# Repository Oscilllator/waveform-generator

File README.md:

# Why does it exist

The purpose of this waveform generator is to give your computer the ability to make waves. It should be thought of as a waveform interface for your computer, like a network interface or an audio interface. The computer streams waveforms continuously to the generator, the generator itself has no memory.
I created this because I don't like the software interface to any other waveform generator I have used.

You use it like this:
```python
import numpy as np
import awglib
awg = awglib.awg()
samples = np.sin(np.linspace(0, 2 * np.pi, 1000))
awg.send_volts(samples)
```

You can simply stream samples to it, or gate the sending of the samples on a trigger input. It also has two digital outputs which are embedded in the sample stream. You can use them like this:

```python
samples = np.sin(np.linspace(0, 2 * np.pi, 1000))
d0 = samples > 0.8
d1 = samples < -0.5
awg.send_volts(samples, digital=[d0, d1])
```

Which then would look like this:

This is useful for triggering your scope or other instruments.

## Specifications
| Parameter           | Value    |
|---------------------|----------|
| Samples rate        | 10 MSa/s |
| Rise/fall time      | 50 ns    |
| Max output current  | 600 mA   |
| Resolution          | 14 bit   |
| Digital outputs     | 2        |

The device also has a 16 bit digital output bus for debugging the fpga, and 8 LED's. The digital outputs come straight from the FPGA and so have no drive strength to speak of. You won't blow up the FPGA if you 50R terminate them, though.

It looks like this:

## Examples

### Scrolling text

This example is `examples/scrolling_text.py` and demonstrates some of the benefits of having a streaming setup - there is a lot of memory on your main computer as compared to any reasonable waveform generator.

This whole gif is one single waveform of about ~500MB over the wire. Several passes are made over the text, one for each letter section. The persistence of vision within the oscilloscope stitches them together, producing whole letters. Once the whole text has been emitted the waveform is then re-emitted with the embedded digital trigger pulse sent with a slightly different time delay. This is easily done by simply concatenating the waveform to itself many times, attaching a shifted version of the trigger array each time. This wastes a lot of memory but was trivial to implement.

## Setup
### From a new computer
#### Udev rules
The USB chip is a FT232, but I have programmed it to have a custom Vid and Pid, so that the linux kernel doesn't grab it.

This script sets up the udev rules so the device can be opened without root:

```./ft/setup.sh```
#### Python library
I install it like this from the root directory of the repository:

```pip install -e .```

That way the library is loaded from the repository on startup rather than being copied to an install directory. Ask your favourite AI what's right for you.

### From a bare PCB
The EEPROM of the FT2332 needs to be programmed so that it will output in synchronous FIFO mode, and so that the default vendor ID and product ID is changed, preventing the linux kernel from recognising it.

```./program_eeprom.sh```

## Repository contents
This repository contains the kicad files, RTL, and API to operate a waveform generator.

### Hardware
I got the PCB's assembled with JLCPCB's 6 layer service with plated over vias, to make the routing of the FPGA BGA package easy.
The device uses an FT232 as a USB->FIFO adapter, that currently streams exclusively in the PC->FT232 direction. Use of the device in this mode requires flashing the eeprom, for which a utility is also included.

### RTL
The Flow of information is as follows:

PC -> FT232 -> ECP5 FPGA -> AD9744 DAC -> Amplifier

The RTL for the fpga is provided, which uses the excellent repository [here](https://github.com/WangXuan95/FPGA-ftdi245fifo/tree/main?tab=readme-ov-file#cn) to interface with the FT232. The AD9744 has a simple parallel interface, so that also makes things easy.

The simulation can be run as a unit test with `./run_tests.sh`

### API
The waveform generator is interfaces with in python, though I may [port it to C](https://harrydb.com/Continuous-waveforms) at some point.

### Bringup notes

This device was designed as a series of sub-boards. It started as a [Colorlight DAC](https://harrydb.com/20240902-A-good-waveform-generator) dev board and the [amplifier stage](https://harrydb.com/20250103-awg-buffer-bringup). These were then merged into a [Single PCB](https://harrydb.com/20250403-AWG-2-bringup). There are [various other notes](https://harrydb.com/#waveform-generator) on my lab notes page that detail other parts of the design process.

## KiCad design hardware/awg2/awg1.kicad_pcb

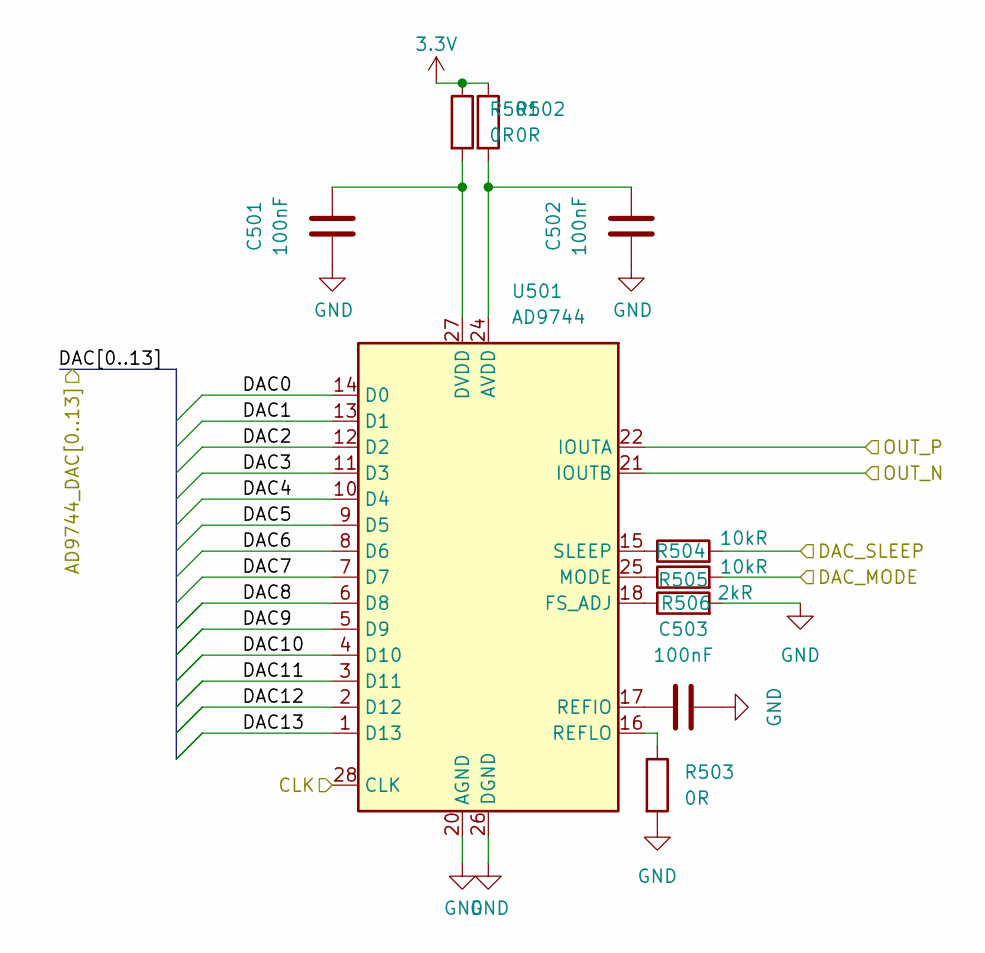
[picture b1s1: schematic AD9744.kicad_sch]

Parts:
C501, C502, C503: 100nF; R_0603_1608Metric; LCSC C1634
R501, R502: 0R; R_0603_1608Metric
R503: 0R; R_0603_1608Metric; LCSC C22787
R504, R505: 10kR; R_0603_1608Metric; LCSC C22787
R506: 2kR; R_0603_1608Metric; LCSC C22787
U501: AD9744; TSSOP-28_4.4x9.7mm_P0.65mm

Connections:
3.3V: R501.1, R502.1; also elsewhere on the board
/AD9744/CLK: U501.28 (CLK); also elsewhere on the board
/AD9744/DAC0: U501.14 (D0); also elsewhere on the board
/AD9744/DAC1: U501.13 (D1); also elsewhere on the board
/AD9744/DAC2: U501.12 (D2); also elsewhere on the board
/AD9744/DAC3: U501.11 (D3); also elsewhere on the board
/AD9744/DAC4: U501.10 (D4); also elsewhere on the board
/AD9744/DAC5: U501.9 (D5); also elsewhere on the board
/AD9744/DAC6: U501.8 (D6); also elsewhere on the board
/AD9744/DAC7: U501.7 (D7); also elsewhere on the board
/AD9744/DAC8: U501.6 (D8); also elsewhere on the board
/AD9744/DAC9: U501.5 (D9); also elsewhere on the board
/AD9744/DAC10: U501.4 (D10); also elsewhere on the board
/AD9744/DAC11: U501.3 (D11); also elsewhere on the board
/AD9744/DAC12: U501.2 (D12); also elsewhere on the board
/AD9744/DAC13: U501.1 (D13); also elsewhere on the board
/AD9744/DAC_MODE: R505.2; also elsewhere on the board
/AD9744/DAC_SLEEP: R504.2; also elsewhere on the board
/AD9744/OUT_N: U501.21 (IOUTB); also elsewhere on the board
/AD9744/OUT_P: U501.22 (IOUTA); also elsewhere on the board
GND: C501.1, C502.1, C503.1, R503.2, R506.2, U501.20 (AGND), U501.26 (DGND); also elsewhere on the board
unnamed: C502.2, R502.2, U501.24 (AVDD)
unnamed: C501.2, R501.2, U501.27 (DVDD)
unnamed: R506.1, U501.18 (FS_ADJ)
unnamed: R505.1, U501.25 (MODE)
unnamed: C503.2, U501.17 (REFIO)
unnamed: R503.1, U501.16 (REFLO)
unnamed: R504.1, U501.15 (SLEEP)

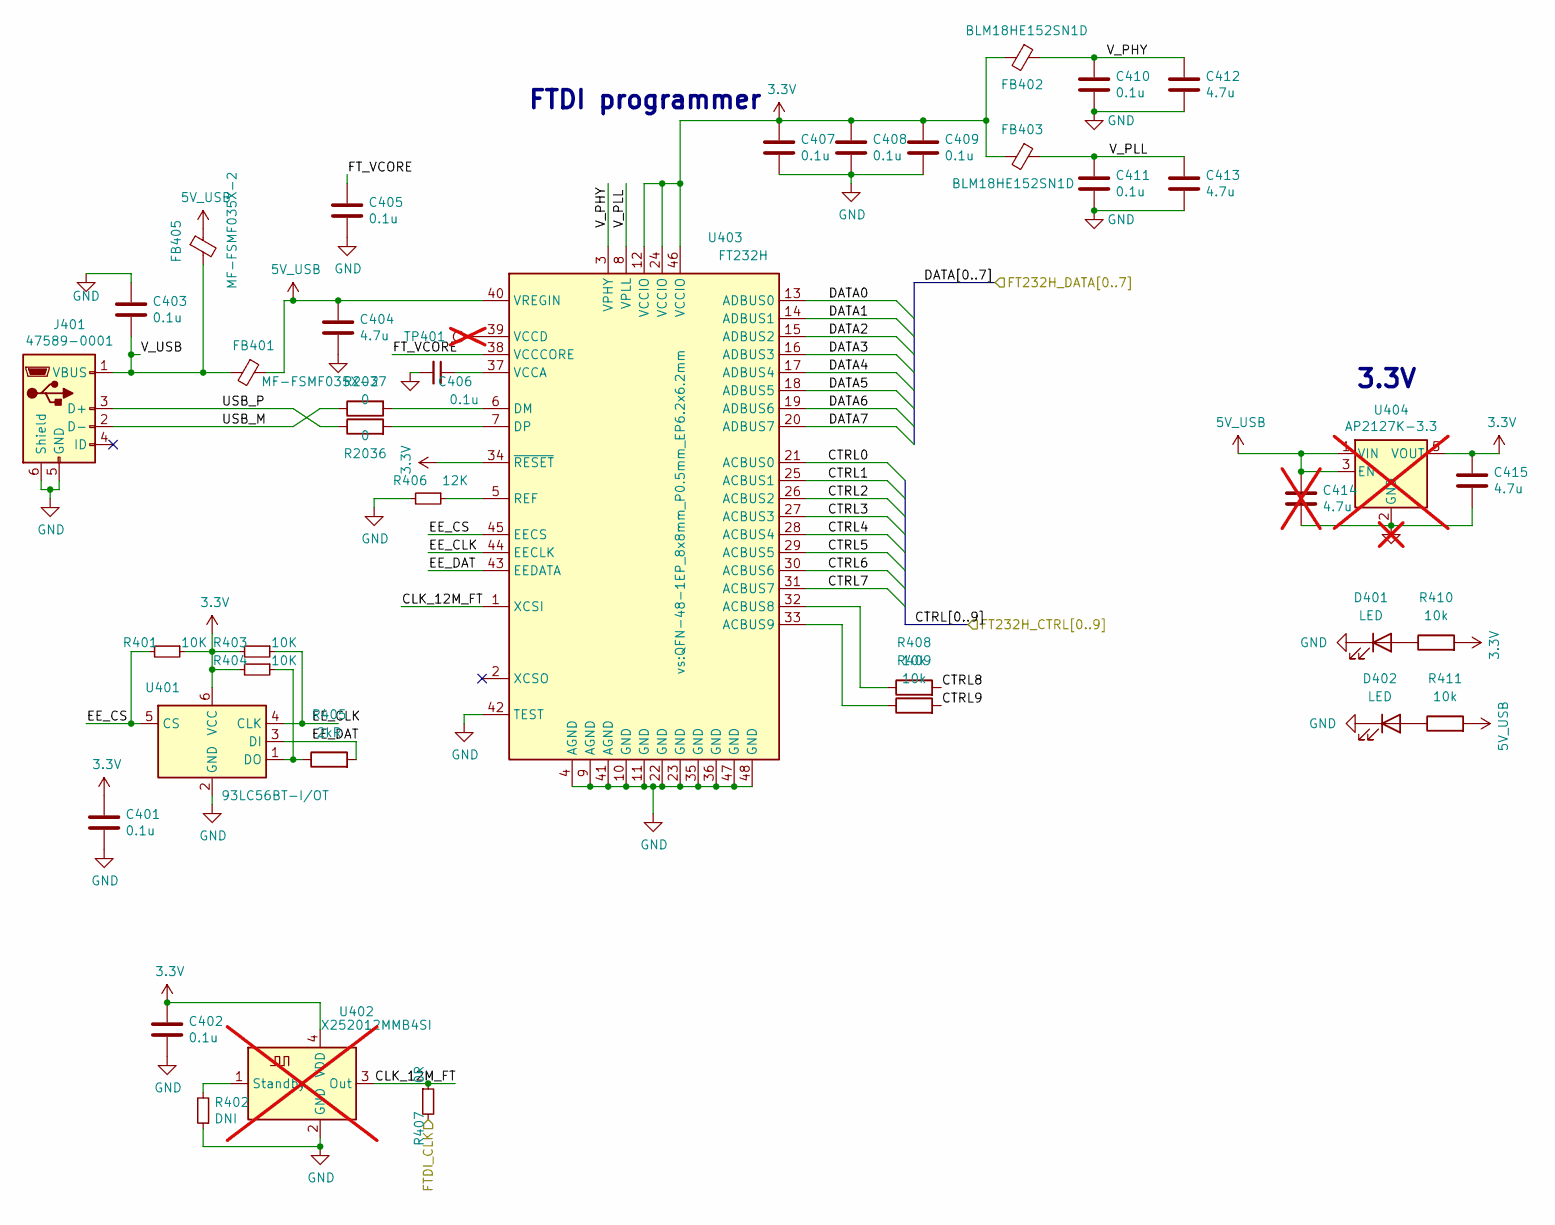
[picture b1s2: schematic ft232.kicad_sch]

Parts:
C401, C402, C403, C405, C406, C407, C408, C409, C410, C411: 0.1u; C_0603_1608Metric
C404, C412, C413, C415: 4.7u; C_0603_1608Metric
C414: 4.7u; C_0603_1608Metric; not fitted
D401, D402: LED; D_0603_1608Metric; LCSC C2286
FB401, FB405: MF-FSMF035X-2; L_0603_1608Metric
FB402, FB403: BLM18HE152SN1D; L_0603_1608Metric
J401: 47589-0001; USB_Micro-B_Molex_47346-0001
R401, R403, R404: 10K; R_0603_1608Metric
R402: DNI; R_0603_1608Metric
R405: 2kR; R_0402_1005Metric
R406: 12K; R_0603_1608Metric
R407: 0R; R_0603_1608Metric
R408, R409, R410, R411: 10k; R_0603_1608Metric; LCSC C25804
R2036, R2037: 0; R_0603_1608Metric; LCSC C21189
TP401: TestPoint; TestPoint_Pad_D1.0mm; not fitted
U401: 93LC56BT-I/OT; SOT-23-6
U402: X252012MMB4SI; Oscillator_SMD_Abracon_ASDMB-4Pin_2.5x2.0mm; not fitted
U403: FT232H; QFN-48-1EP_8x8mm_P0.5mm_EP6.2x6.2mm
U404: AP2127K-3.3; SOT-23-5; not fitted

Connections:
3.3V: C401.1, C402.1, C407.1, C408.1, C409.1, C415.1, FB402.2, FB403.2, R401.1, R403.2, R404.2, R410.2, U401.6 (VCC), U402.4 (VDD), U403.12 (VCCIO), U403.24 (VCCIO), U403.34 (~RESET), U403.46 (VCCIO), U404.5 (VOUT); also elsewhere on the board
5V_USB: C404.1, C414.1, FB401.1, FB405.1, R411.2, U403.40 (VREGIN), U404.1 (VIN), U404.3 (EN); also elsewhere on the board
/fpga/CTRL0: U403.21 (ACBUS0); also elsewhere on the board
/fpga/CTRL1: U403.25 (ACBUS1); also elsewhere on the board
/fpga/CTRL2: U403.26 (ACBUS2); also elsewhere on the board
/fpga/CTRL3: U403.27 (ACBUS3); also elsewhere on the board
/fpga/CTRL4: U403.28 (ACBUS4); also elsewhere on the board
/fpga/CTRL5: U403.29 (ACBUS5); also elsewhere on the board
/fpga/CTRL6: U403.30 (ACBUS6); also elsewhere on the board
/fpga/CTRL7: U403.31 (ACBUS7); also elsewhere on the board
/fpga/CTRL8: R408.2; also elsewhere on the board
/fpga/CTRL9: R409.2; also elsewhere on the board
/fpga/DATA0: U403.13 (ADBUS0); also elsewhere on the board
/fpga/DATA1: U403.14 (ADBUS1); also elsewhere on the board
/fpga/DATA2: U403.15 (ADBUS2); also elsewhere on the board
/fpga/DATA3: U403.16 (ADBUS3); also elsewhere on the board
/fpga/DATA4: U403.17 (ADBUS4); also elsewhere on the board
/fpga/DATA5: U403.18 (ADBUS5); also elsewhere on the board
/fpga/DATA6: U403.19 (ADBUS6); also elsewhere on the board
/fpga/DATA7: U403.20 (ADBUS7); also elsewhere on the board
/fpga/FTDI_CLK: R407.2; also elsewhere on the board
/ft232/CLK_12M_FT: R407.1, U402.3 (Out), U403.1 (XCSI)
/ft232/EE_CLK: R403.1, U401.4 (CLK), U403.44 (EECLK)
/ft232/EE_CS: R401.2, U401.5 (CS), U403.45 (EECS)
/ft232/EE_DAT: R405.2, U401.3 (DI), U403.43 (EEDATA)
/ft232/FT_VCORE: C405.1, U403.38 (VCCCORE)
/ft232/USB_M: J401.2 (D-), R2036.1
/ft232/USB_P: J401.3 (D+), R2037.1
/ft232/V_PHY: C410.1, C412.1, FB402.1, U403.3 (VPHY)
/ft232/V_PLL: C411.1, C413.1, FB403.1, U403.8 (VPLL)
/ft232/V_USB: C403.2, FB401.2, FB405.2, J401.1 (VBUS)
GND: C401.2, C402.2, C403.1, C404.2, C405.2, C406.2, C407.2, C408.2, C409.2, C410.2, C411.2, C412.2, C413.2, C414.2, C415.2, D401.1 (K), D402.1 (K), J401.5 (GND), J401.6 (Shield), R402.1, R406.2, U401.2 (GND), U402.2 (GND), U403.4 (AGND), U403.9 (AGND), U403.10 (GND), U403.11 (GND), U403.22 (GND), U403.23 (GND), U403.35 (GND), U403.36 (GND), U403.41 (AGND), U403.42 (TEST), U403.47 (GND), U403.48 (GND), U404.2 (GND); also elsewhere on the board
unnamed: D401.2 (A), R410.1
unnamed: D402.2 (A), R411.1
unnamed: R404.1, R405.1, U401.1 (DO)
unnamed: R402.2, U402.1 (Standby)
unnamed: R408.1, U403.32 (ACBUS8)
unnamed: R409.1, U403.33 (ACBUS9)
unnamed: R2036.2, U403.6 (DM)
unnamed: R2037.2, U403.7 (DP)
unnamed: R406.1, U403.5 (REF)
unnamed: C406.1, U403.37 (VCCA)
unnamed: TP401.1, U403.39 (VCCD)

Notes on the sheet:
3.3V
FTDI programmer

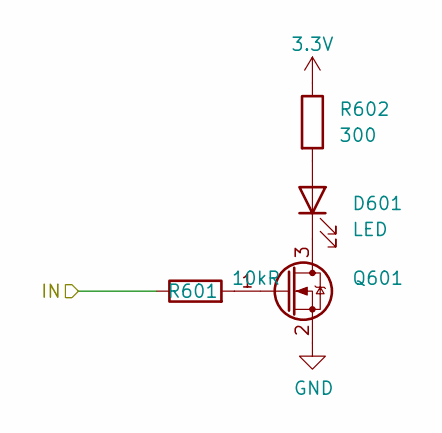
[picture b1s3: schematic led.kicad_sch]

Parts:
D601: LED; D_0603_1608Metric
Q601: Q_NMOS_Depletion_GSD; SOT-23; LCSC C20917
R601: 10kR; R_0603_1608Metric; LCSC C22787
R602: 300; R_0603_1608Metric_Pad0.98x0.95mm_HandSolder

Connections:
3.3V: R602.1; also elsewhere on the board
/lED0: R601.1; also elsewhere on the board
GND: Q601.2 (S); also elsewhere on the board
unnamed: D601.2 (A), R602.2
unnamed: D601.1 (K), Q601.3 (D)
unnamed: Q601.1 (G), R601.2

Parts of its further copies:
D701, D801, D901, D1001, D1101, D1201, D1301: LED; D_0603_1608Metric
Q701, Q801, Q901, Q1001, Q1101, Q1201, Q1301: Q_NMOS_Depletion_GSD; SOT-23; LCSC C20917
R701, R801, R901, R1001, R1101, R1201, R1301: 10kR; R_0603_1608Metric; LCSC C22787
R702, R802, R902, R1002, R1102, R1202, R1302: 300; R_0603_1608Metric_Pad0.98x0.95mm_HandSolder

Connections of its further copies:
3.3V: R702.1, R802.1, R902.1, R1002.1, R1102.1, R1202.1, R1302.1; also elsewhere on the board
/lED1: R701.1; also elsewhere on the board
/lED2: R801.1; also elsewhere on the board
/lED3: R901.1; also elsewhere on the board
/lED4: R1001.1; also elsewhere on the board
/lED5: R1101.1; also elsewhere on the board
/lED6: R1201.1; also elsewhere on the board
/lED7: R1301.1; also elsewhere on the board
GND: Q701.2 (S), Q801.2 (S), Q901.2 (S), Q1001.2 (S), Q1101.2 (S), Q1201.2 (S), Q1301.2 (S); also elsewhere on the board
unnamed: D701.2 (A), R702.2
unnamed: D701.1 (K), Q701.3 (D)
unnamed: D801.2 (A), R802.2
unnamed: D801.1 (K), Q801.3 (D)
unnamed: D901.2 (A), R902.2
unnamed: D901.1 (K), Q901.3 (D)
unnamed: D1001.2 (A), R1002.2
unnamed: D1001.1 (K), Q1001.3 (D)
unnamed: D1101.2 (A), R1102.2
unnamed: D1101.1 (K), Q1101.3 (D)
unnamed: D1201.2 (A), R1202.2
unnamed: D1201.1 (K), Q1201.3 (D)
unnamed: D1301.2 (A), R1302.2
unnamed: D1301.1 (K), Q1301.3 (D)
unnamed: Q701.1 (G), R701.2
unnamed: Q801.1 (G), R801.2
unnamed: Q901.1 (G), R901.2
unnamed: Q1001.1 (G), R1001.2
unnamed: Q1101.1 (G), R1101.2
unnamed: Q1201.1 (G), R1201.2
unnamed: Q1301.1 (G), R1301.2

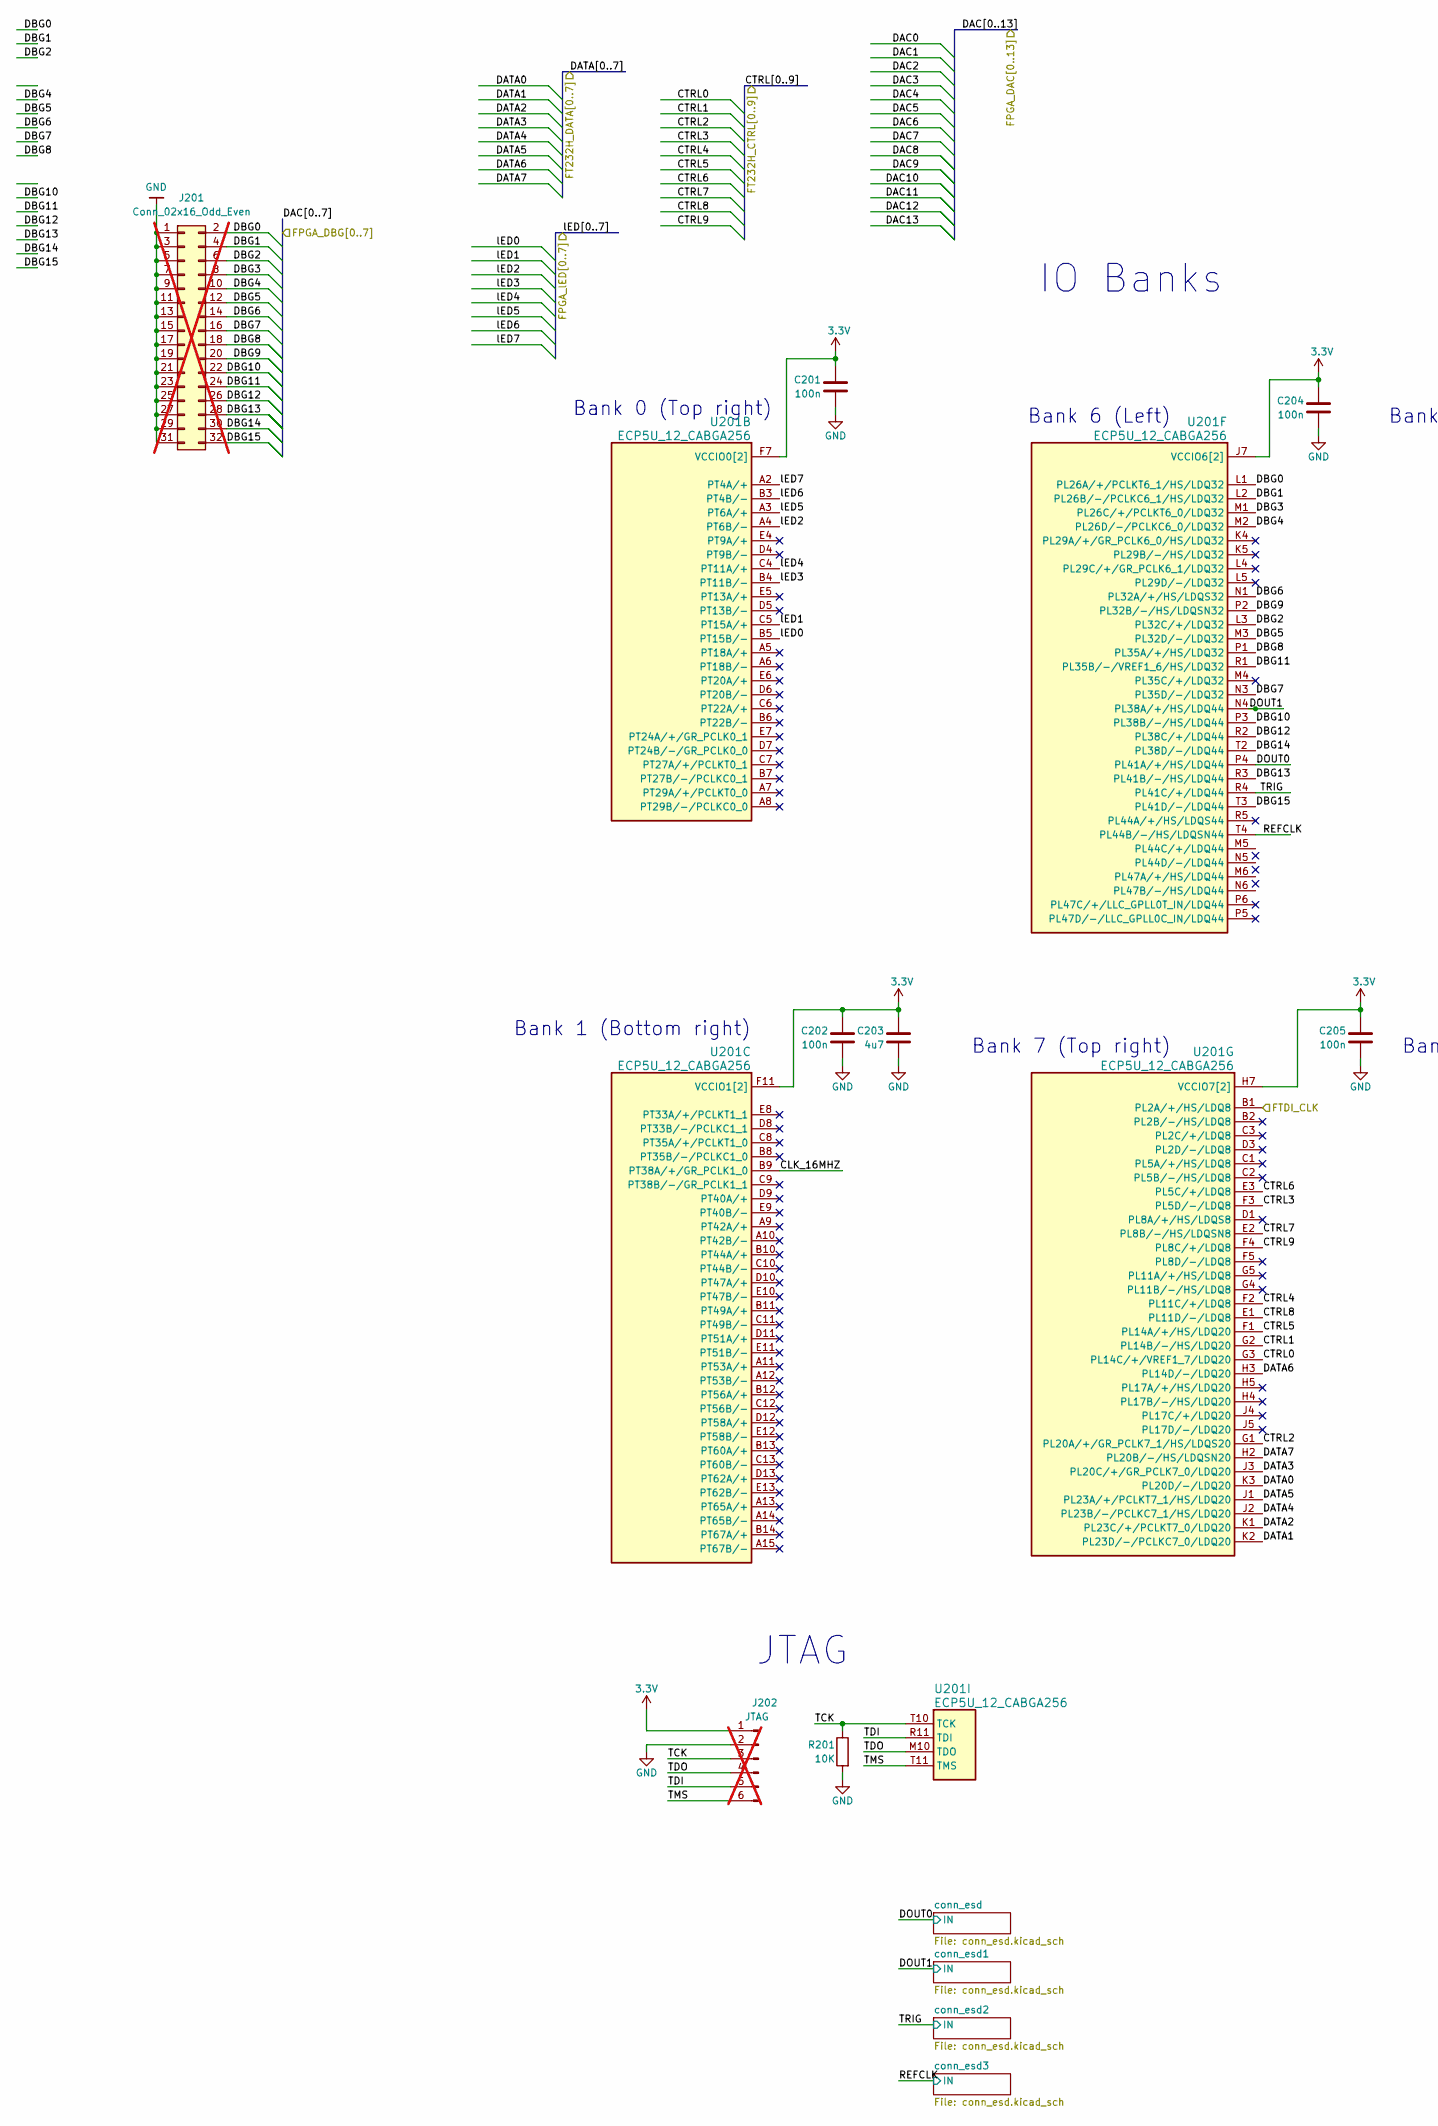
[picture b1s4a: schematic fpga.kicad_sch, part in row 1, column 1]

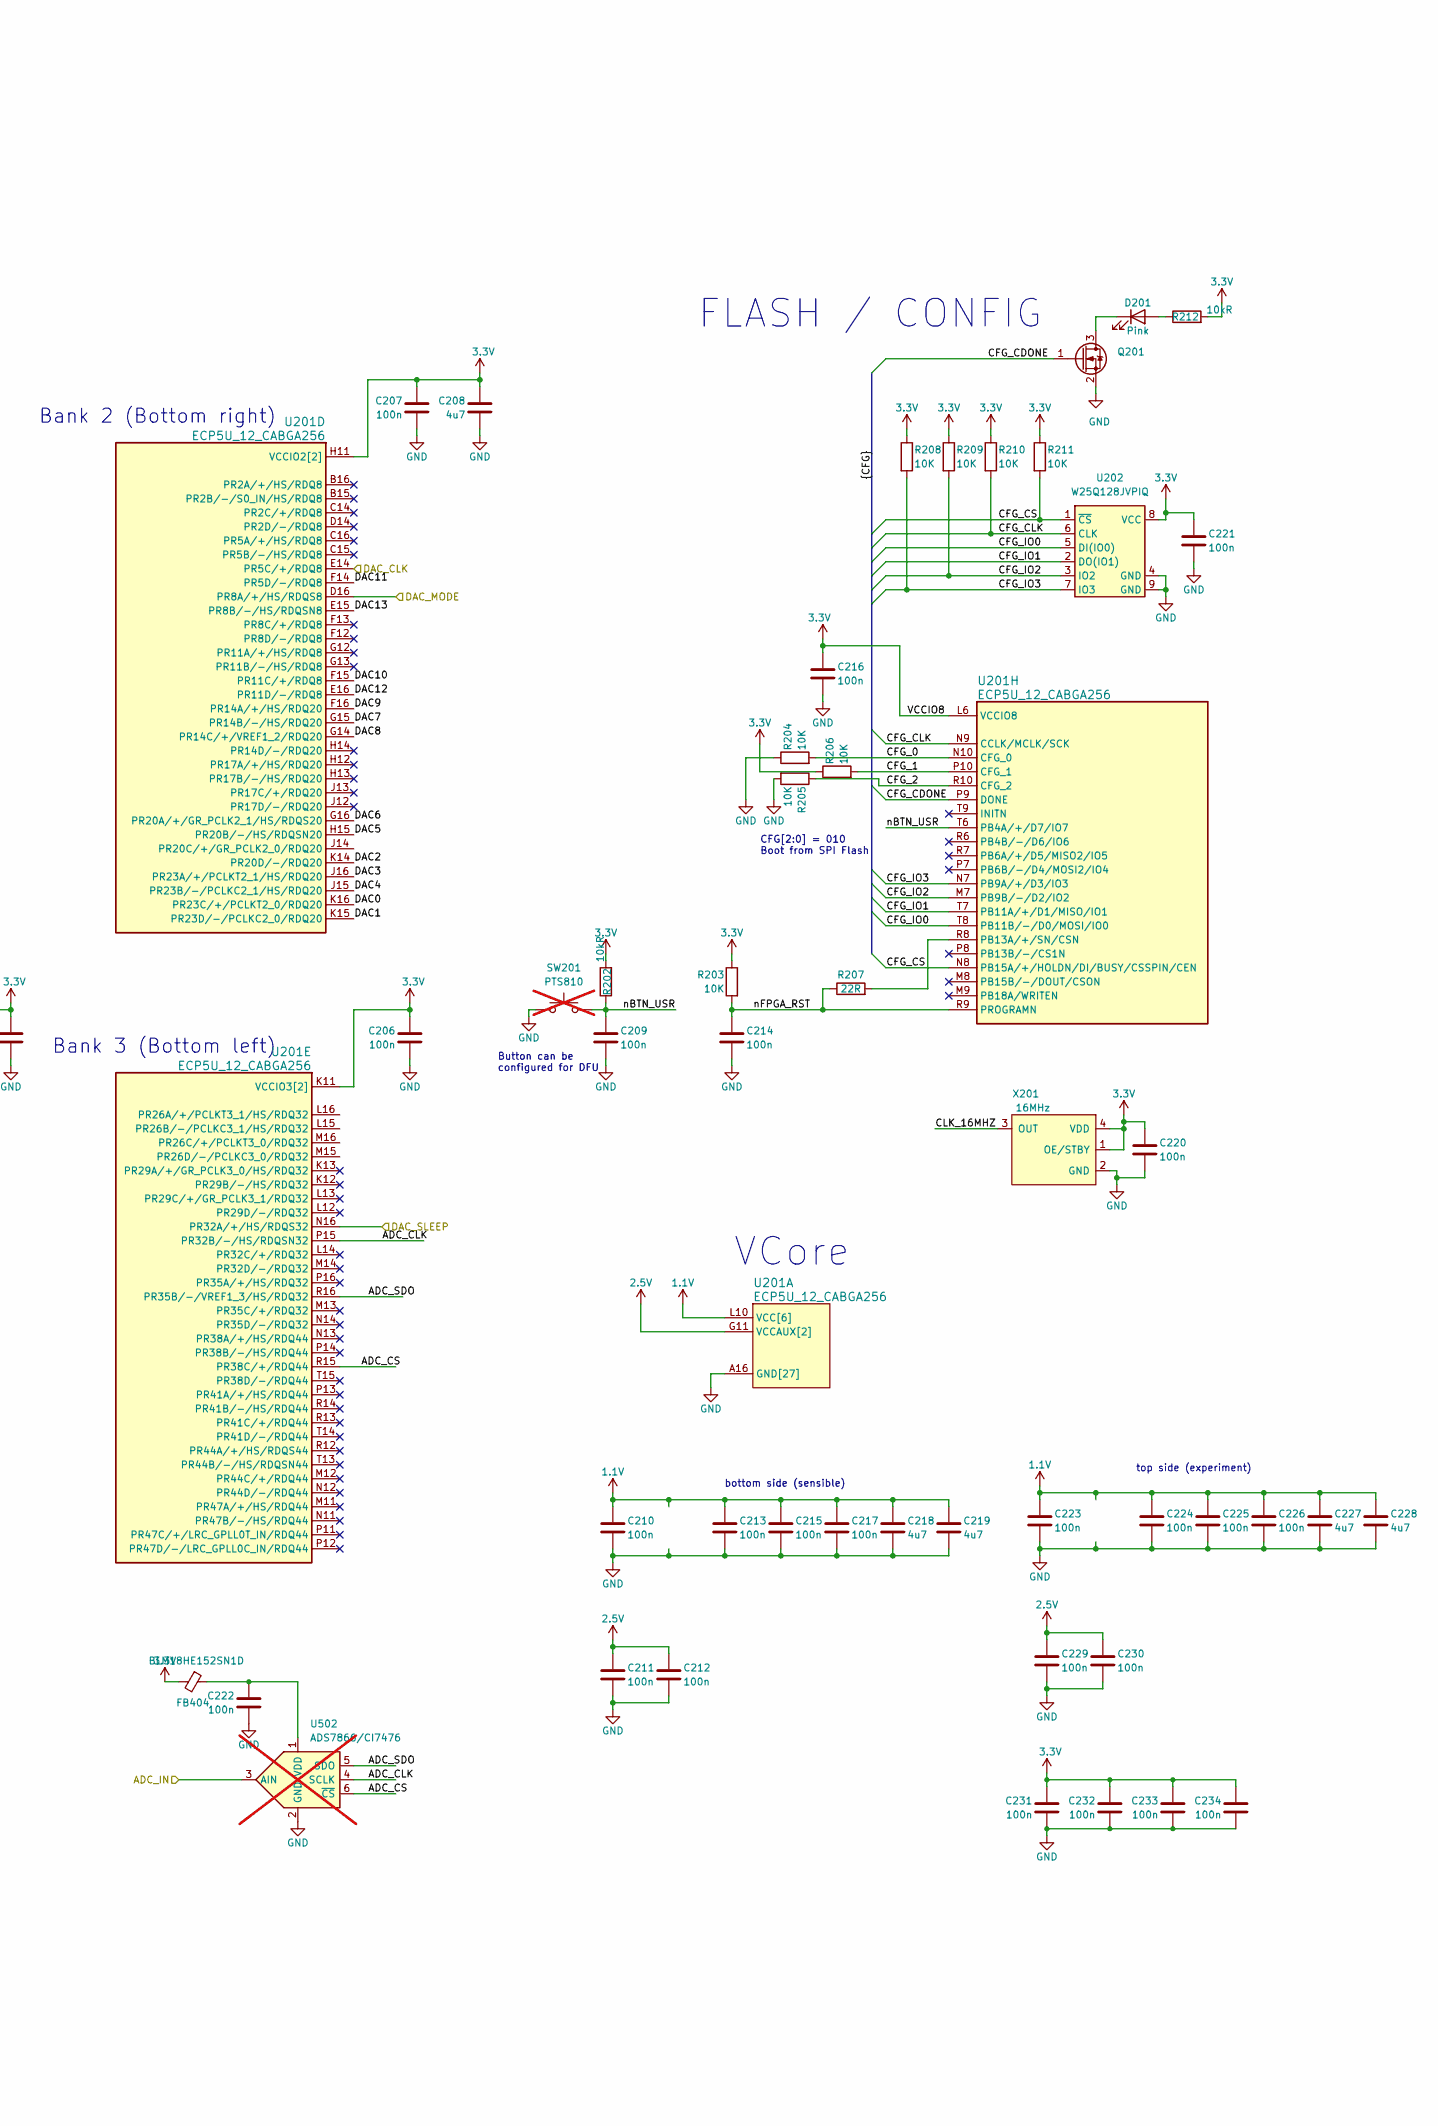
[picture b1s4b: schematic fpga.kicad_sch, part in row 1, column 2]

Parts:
C201, C202, C204, C205, C206, C207, C210, C211, C212, C213, C215, C216, C217, C220, C221, C222, C223, C224, C225, C226, C229, C230, C231, C232, C233, C234: 100n; C_0402_1005Metric; MPN CC0402KRX7R7BB104; LCSC C327009
C203, C208, C218, C219, C227, C228: 4u7; C_0402_1005Metric; MPN CC0402KRX5R6BB475; LCSC C326586
C209, C214: 100n; C_0402_1005Metric; MPN CC0402KRX7R7BB104
D201: Pink; LED_0603_1608Metric; MPN OSK40603C1E; LCSC C268294
FB404: BLM18HE152SN1D; L_0603_1608Metric
J201: Conn_02x16_Odd_Even; PinHeader_2x16_P2.54mm_Vertical; not fitted
J202: JTAG; STM_6_PIN_THT_Staggered; not fitted
Q201: Q_NMOS_Depletion_GSD; SOT-23; LCSC C20917
R201, R203, R204, R205, R206, R208, R209, R210, R211: 10K; R_0402_1005Metric; MPN RC0402JR-0710KL; LCSC C60489
R202, R212: 10kR; R_0603_1608Metric; LCSC C22787
R207: 22R; R_0402_1005Metric; MPN RC0402JR-0722RL
SW201: PTS810; SW_SPST_PTS810; MPN PTS810 SJM 250 SMTR LFS; LCSC C116501; not fitted
U201: ECP5U_12_CABGA256; BGA-256_14.0x14.0mm_Layout16x16_P0.8mm_Ball0.45mm_Pad0.32mm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; MPN LFE5U12F8BG256C
U202: W25Q128JVPIQ; WSON-8-1EP_6x5mm_P1.27mm_EP3.4x4.3mm; MPN W25Q128JVPIQ; LCSC C190862
U502: ADS7866/CI7476; TSOT-23-6; not fitted
X201: 16MHz; CDFN_3.2x2.5mm_XO; MPN DSC6101CI2A-016.0000

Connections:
1.1V: C210.1, C213.1, C215.1, C217.1, C218.1, C219.1, C223.1, C224.1, C225.1, C226.1, C227.1, C228.1, U201.G6 (VCC[6]), U201.G7 (VCC[6]), U201.G9 (VCC[6]), U201.L8 (VCC[6]), U201.L9 (VCC[6]), U201.L10 (VCC[6]); also elsewhere on the board
2.5V: C211.1, C212.1, C229.1, C230.1, U201.G11 (VCCAUX[2]), U201.L7 (VCCAUX[2]); also elsewhere on the board
3.3V: C201.1, C202.1, C203.1, C204.1, C205.1, C206.1, C207.1, C208.1, C216.1, C220.1, C221.1, C231.1, C232.1, C233.1, C234.1, FB404.2, J202.1, R202.2, R203.1, R206.1, R208.1, R209.1, R210.1, R211.1, R212.2, U201.F6 (VCCIO0[2]), U201.F7 (VCCIO0[2]), U201.F10 (VCCIO1[2]), U201.F11 (VCCIO1[2]), U201.H6 (VCCIO7[2]), U201.H7 (VCCIO7[2]), U201.H11 (VCCIO2[2]), U201.J6 (VCCIO6[2]), U201.J7 (VCCIO6[2]), U201.J11 (VCCIO2[2]), U201.K11 (VCCIO3[2]), U201.L6 (VCCIO8), U201.L11 (VCCIO3[2]), U202.8 (VCC), X201.1 (OE/STBY), X201.4 (VDD); also elsewhere on the board
/AD9744/CLK: U201.E14 (PR5C/+/RDQ8); also elsewhere on the board
/AD9744/DAC0: U201.K16 (PR23C/+/PCLKT2_0/RDQ20); also elsewhere on the board
/AD9744/DAC1: U201.K15 (PR23D/-/PCLKC2_0/RDQ20); also elsewhere on the board
/AD9744/DAC2: U201.K14 (PR20D/-/RDQ20); also elsewhere on the board
/AD9744/DAC3: U201.J16 (PR23A/+/PCLKT2_1/HS/RDQ20); also elsewhere on the board
/AD9744/DAC4: U201.J15 (PR23B/-/PCLKC2_1/HS/RDQ20); also elsewhere on the board
/AD9744/DAC5: U201.H15 (PR20B/-/HS/RDQSN20); also elsewhere on the board
/AD9744/DAC6: U201.G16 (PR20A/+/GR_PCLK2_1/HS/RDQS20); also elsewhere on the board
/AD9744/DAC7: U201.G15 (PR14B/-/HS/RDQ20); also elsewhere on the board
/AD9744/DAC8: U201.G14 (PR14C/+/VREF1_2/RDQ20); also elsewhere on the board
/AD9744/DAC9: U201.F16 (PR14A/+/HS/RDQ20); also elsewhere on the board
/AD9744/DAC10: U201.F15 (PR11C/+/RDQ8); also elsewhere on the board
/AD9744/DAC11: U201.F14 (PR5D/-/RDQ8); also elsewhere on the board
/AD9744/DAC12: U201.E16 (PR11D/-/RDQ8); also elsewhere on the board
/AD9744/DAC13: U201.E15 (PR8B/-/HS/RDQSN8); also elsewhere on the board
/AD9744/DAC_MODE: U201.D16 (PR8A/+/HS/RDQS8); also elsewhere on the board
/AD9744/DAC_SLEEP: U201.N16 (PR32A/+/HS/RDQS32); also elsewhere on the board
/awg_amp/OUT_SLOW: U502.3 (AIN); also elsewhere on the board
/fpga/ADC_CLK: U201.P15 (PR32B/-/HS/RDQSN32), U502.4 (SCLK)
/fpga/ADC_CS: U201.R15 (PR38C/+/RDQ44), U502.6 (~CS)
/fpga/ADC_SDO: U201.R16 (PR35B/-/VREF1_3/HS/RDQ32), U502.5 (SDO)
/fpga/CFG_0: R204.2, U201.N10 (CFG_0)
/fpga/CFG_1: R206.2, U201.P10 (CFG_1)
/fpga/CFG_2: R205.1, U201.R10 (CFG_2)
/fpga/CFG_CDONE: Q201.1 (G), U201.P9 (DONE)
/fpga/CFG_CLK: R210.2, U201.N9 (CCLK/MCLK/SCK), U202.6 (CLK)
/fpga/CFG_CS: R211.2, U201.N8 (PB15A/+/HOLDN/DI/BUSY/CSSPIN/CEN), U202.1 (~CS)
/fpga/CFG_IO0: U201.T8 (PB11B/-/D0/MOSI/IO0), U202.5 (DI(IO0))
/fpga/CFG_IO1: U201.T7 (PB11A/+/D1/MISO/IO1), U202.2 (DO(IO1))
/fpga/CFG_IO2: R209.2, U201.M7 (PB9B/-/D2/IO2), U202.3 (IO2)
/fpga/CFG_IO3: R208.2, U201.N7 (PB9A/+/D3/IO3), U202.7 (IO3)
/fpga/CLK_16MHZ: U201.B9 (PT38A/+/GR_PCLK1_0), X201.3 (OUT)
/fpga/CTRL0: U201.G3 (PL14C/+/VREF1_7/LDQ20); also elsewhere on the board
/fpga/CTRL1: U201.G2 (PL14B/-/HS/LDQ20); also elsewhere on the board
/fpga/CTRL2: U201.G1 (PL20A/+/GR_PCLK7_1/HS/LDQS20); also elsewhere on the board
/fpga/CTRL3: U201.F3 (PL5D/-/LDQ8); also elsewhere on the board
/fpga/CTRL4: U201.F2 (PL11C/+/LDQ8); also elsewhere on the board
/fpga/CTRL5: U201.F1 (PL14A/+/HS/LDQ20); also elsewhere on the board
/fpga/CTRL6: U201.E3 (PL5C/+/LDQ8); also elsewhere on the board
/fpga/CTRL7: U201.E2 (PL8B/-/HS/LDQSN8); also elsewhere on the board
/fpga/CTRL8: U201.E1 (PL11D/-/LDQ8); also elsewhere on the board
/fpga/CTRL9: U201.F4 (PL8C/+/LDQ8); also elsewhere on the board
/fpga/DATA0: U201.K3 (PL20D/-/LDQ20); also elsewhere on the board
/fpga/DATA1: U201.K2 (PL23D/-/PCLKC7_0/LDQ20); also elsewhere on the board
/fpga/DATA2: U201.K1 (PL23C/+/PCLKT7_0/LDQ20); also elsewhere on the board
/fpga/DATA3: U201.J3 (PL20C/+/GR_PCLK7_0/LDQ20); also elsewhere on the board
/fpga/DATA4: U201.J2 (PL23B/-/PCLKC7_1/HS/LDQ20); also elsewhere on the board
/fpga/DATA5: U201.J1 (PL23A/+/PCLKT7_1/HS/LDQ20); also elsewhere on the board
/fpga/DATA6: U201.H3 (PL14D/-/LDQ20); also elsewhere on the board
/fpga/DATA7: U201.H2 (PL20B/-/HS/LDQSN20); also elsewhere on the board
/fpga/DBG0: J201.2, U201.L1 (PL26A/+/PCLKT6_1/HS/LDQ32)
/fpga/DBG1: J201.4, U201.L2 (PL26B/-/PCLKC6_1/HS/LDQ32)
/fpga/DBG2: J201.6, U201.L3 (PL32C/+/LDQ32)
/fpga/DBG3: J201.8, U201.M1 (PL26C/+/PCLKT6_0/LDQ32)
/fpga/DBG4: J201.10, U201.M2 (PL26D/-/PCLKC6_0/LDQ32)
/fpga/DBG5: J201.12, U201.M3 (PL32D/-/LDQ32)
/fpga/DBG6: J201.14, U201.N1 (PL32A/+/HS/LDQS32)
/fpga/DBG7: J201.16, U201.N3 (PL35D/-/LDQ32)
/fpga/DBG8: J201.18, U201.P1 (PL35A/+/HS/LDQ32)
/fpga/DBG9: J201.20, U201.P2 (PL32B/-/HS/LDQSN32)
/fpga/DBG10: J201.22, U201.P3 (PL38B/-/HS/LDQ44)
/fpga/DBG11: J201.24, U201.R1 (PL35B/-/VREF1_6/HS/LDQ32)
/fpga/DBG12: J201.26, U201.R2 (PL38C/+/LDQ44)
/fpga/DBG13: J201.28, U201.R3 (PL41B/-/HS/LDQ44)
/fpga/DBG14: J201.30, U201.T2 (PL38D/-/LDQ44)
/fpga/DBG15: J201.32, U201.T3 (PL41D/-/LDQ44)
/fpga/DOUT0: U201.P4 (PL41A/+/HS/LDQ44); also elsewhere on the board
/fpga/DOUT1: U201.N4 (PL38A/+/HS/LDQ44); also elsewhere on the board
/fpga/FTDI_CLK: U201.B1 (PL2A/+/HS/LDQ8); also elsewhere on the board
/fpga/REFCLK: U201.T4 (PL44B/-/HS/LDQSN44); also elsewhere on the board
/fpga/TCK: J202.3, R201.1, U201.T10 (TCK)
/fpga/TDI: J202.5, U201.R11 (TDI)
/fpga/TDO: J202.4, U201.M10 (TDO)
/fpga/TMS: J202.6, U201.T11 (TMS)
/fpga/TRIG: U201.R4 (PL41C/+/LDQ44); also elsewhere on the board
/fpga/nBTN_USR: C209.1, R202.1, SW201.2, U201.T6 (PB4A/+/D7/IO7)
/fpga/nFPGA_RST: C214.1, R203.2, R207.1, U201.R9 (PROGRAMN)
/lED0: U201.B5 (PT15B/-); also elsewhere on the board
/lED1: U201.C5 (PT15A/+); also elsewhere on the board
/lED2: U201.A4 (PT6B/-); also elsewhere on the board
/lED3: U201.B4 (PT11B/-); also elsewhere on the board
/lED4: U201.C4 (PT11A/+); also elsewhere on the board
/lED5: U201.A3 (PT6A/+); also elsewhere on the board
/lED6: U201.B3 (PT4B/-); also elsewhere on the board
/lED7: U201.A2 (PT4A/+); also elsewhere on the board
GND: C201.2, C202.2, C203.2, C204.2, C205.2, C206.2, C207.2, C208.2, C209.2, C210.2, C211.2, C212.2, C213.2, C214.2, C215.2, C216.2, C217.2, C218.2, C219.2, C220.2, C221.2, C222.2, C223.2, C224.2, C225.2, C226.2, C227.2, C228.2, C229.2, C230.2, C231.2, C232.2, C233.2, C234.2, J201.1, J201.3, J201.5, J201.7, J201.9, J201.11, J201.13, J201.15, J201.17, J201.19, J201.21, J201.23, J201.25, J201.27, J201.29, J201.31, J202.2, Q201.2 (S), R201.2, R204.1, R205.2, SW201.1, U201.A1 (GND[27]), U201.A16 (GND[27]), U201.D2 (GND[27]), U201.D15 (GND[27]), U201.F8 (GND[27]), U201.F9 (GND[27]), U201.G8 (GND[27]), U201.G10 (GND[27]), U201.H1 (GND[27]), U201.H8 (GND[27]), U201.H9 (GND[27]), U201.H10 (GND[27]), U201.H16 (GND[27]), U201.J8 (GND[27]), U201.J9 (GND[27]), U201.J10 (GND[27]), U201.K6 (GND[27]), U201.K7 (GND[27]), U201.K8 (GND[27]), U201.K9 (GND[27]), U201.K10 (GND[27]), U201.N2 (GND[27]), U201.N15 (GND[27]), U201.T1 (GND[27]), U201.T5 (GND[27]), U201.T12 (GND[27]), U201.T16 (GND[27]), U202.4 (GND), U202.9 (GND), U502.2 (GND), X201.2 (GND); also elsewhere on the board
unnamed: D201.2 (A), R212.1
unnamed: D201.1 (K), Q201.3 (D)
unnamed: R207.2, U201.R8 (PB13A/+/SN/CSN)
unnamed: C222.1, FB404.1, U502.1 (VDD)

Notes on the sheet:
CFG[2:0] = 010 Boot from SPI Flash
Bank 0 (Top right)
bottom side (sensible)
VCore
top side (experiment)
FLASH / CONFIG
JTAG
Bank 2 (Bottom right)
IO Banks
Bank 1 (Bottom right)
Bank 7 (Top right)
Button can be configured for DFU
Bank 3 (Bottom left)
Bank 6 (Left)
